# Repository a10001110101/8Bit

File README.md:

# 8Bit
Everything 8 bit

Guess.bas - Basic (ehhh?) guessing game for Atari 800

Guess.d64 - Basic (booo) guessing game for Commodore 64

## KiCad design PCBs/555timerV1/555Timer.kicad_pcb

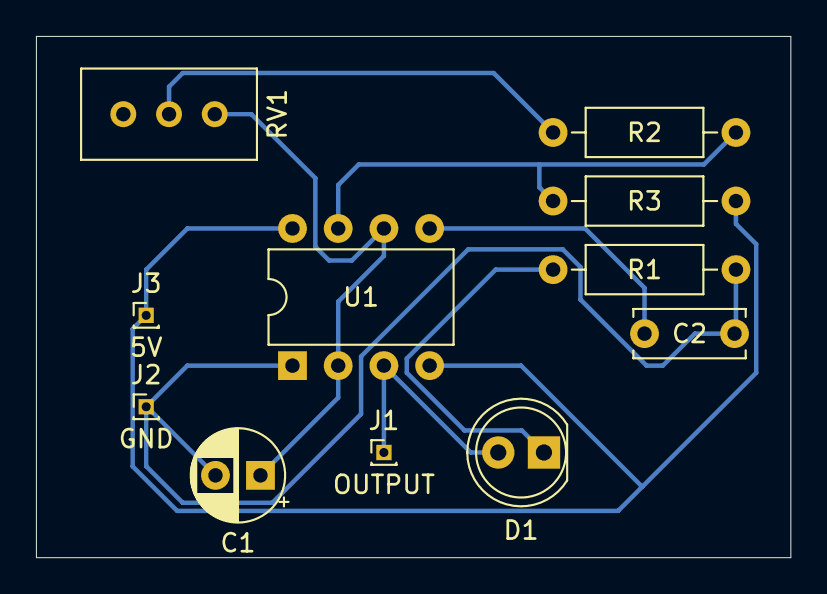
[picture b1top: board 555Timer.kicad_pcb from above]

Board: 2 copper layers, 41.9 x 29.0 mm, 11 parts (0 on the bottom side), 8 nets.

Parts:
C1: 1uF; CP_Radial_D5.0mm_P2.50mm
C2: 0.01uF; C_Disc_D6.0mm_W2.5mm_P5.00mm
D1: YELLOW; LED_D5.0mm
J1: OUTPUT; PinHeader_1x01_P1.00mm_Vertical
J2: GND; PinHeader_1x01_P1.00mm_Vertical
J3: 5V; PinHeader_1x01_P1.00mm_Vertical
R1: 220; R_Axial_DIN0207_L6.3mm_D2.5mm_P10.16mm_Horizontal
R2, R3: 1K; R_Axial_DIN0207_L6.3mm_D2.5mm_P10.16mm_Horizontal
RV1: 1M; Potentiometer_Bourns_3386C_Horizontal
U1: LM555CN; DIP-8_W7.62mm

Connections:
+5V: J3.1, R3.1, U1.4, U1.8
GND: C1.2, C2.2, J2.1, R1.1, U1.1
unnamed: C1.1, RV1.1, U1.2, U1.6
unnamed: C2.1, U1.5
unnamed: D1.1, R1.2
unnamed: D1.2, J1.1, U1.3
unnamed: R2.1, RV1.2
unnamed: R2.2, R3.2, U1.7

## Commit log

2020-04-07 Update LICENSE
2020-04-23 Add files via upload
    Basic (ehhh?) guessing game for the Atari 800
2020-04-23 Add files via upload
    Basic (booo) guessing game for Commodore 64
2020-09-25 555 Timer PCB files ver1
